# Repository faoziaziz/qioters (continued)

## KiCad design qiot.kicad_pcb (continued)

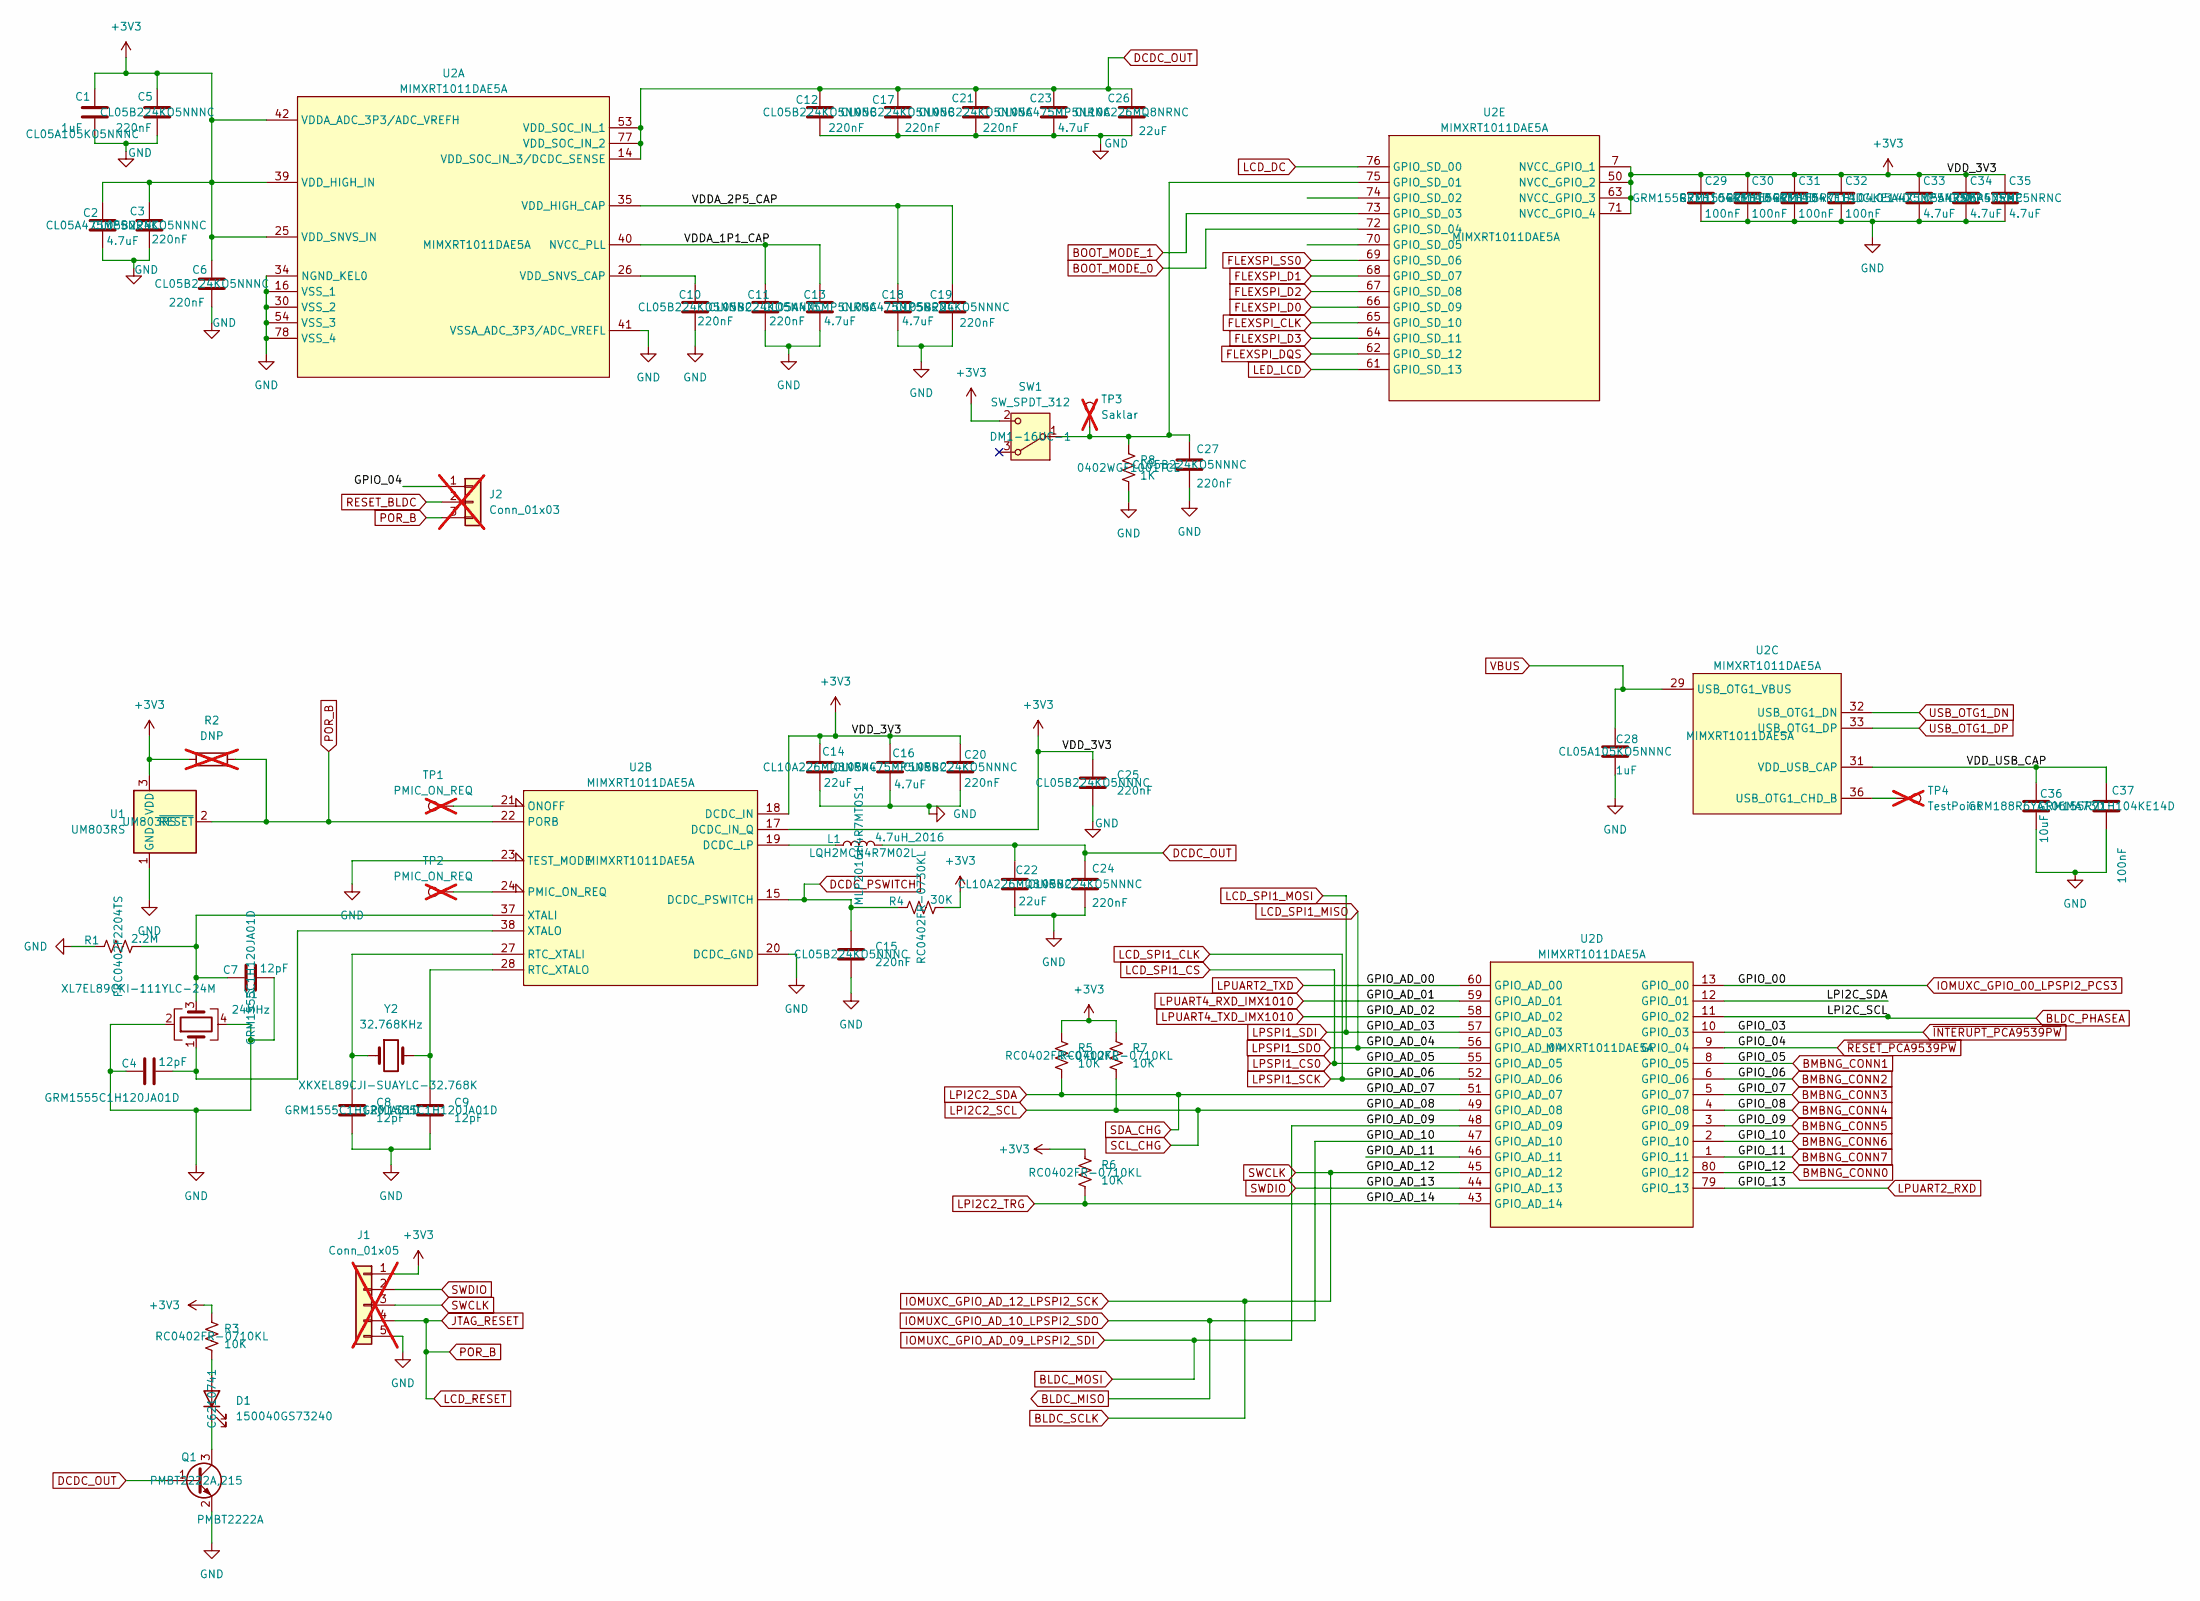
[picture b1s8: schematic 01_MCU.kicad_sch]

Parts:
C1, C28: 1uF; C_0402_1005Metric; Manufacturer_Part_Number CL05A105KO5NNNC; LCSC Part # C29266
C2, C13, C16, C18, C23, C33, C34, C35: 4.7uF; C_0402_1005Metric; Manufacturer_Part_Number CL05A475MP5NRNC; LCSC Part # C23733
C3, C5, C6, C10, C11, C12, C15, C17, C19, C20, C21, C24, C25, C27: 220nF; C_0402_1005Metric; Manufacturer_Part_Number CL05B224KO5NNNC; LCSC Part # C16772
C4, C7, C8, C9: 12pF; C_0402_1005Metric; Manufacturer_Part_Number GRM1555C1H120JA01D; LCSC Part # C76948
C14, C22, C26: 22uF; C_0603_1608Metric; Manufacturer_Part_Number CL10A226MQ8NRNC; LCSC Part # C59461
C29, C30, C31, C32, C37: 100nF; C_0402_1005Metric; Manufacturer_Part_Number GRM155R71H104KE14D; LCSC Part # C77020
C36: 10uF; C_0603_1608Metric; Manufacturer_Part_Number GRM188R6YA106MA73D; LCSC Part # C194427
D1: 150040GS73240; LED_0402_1005Metric; Manufacturer_Part_Number C6210741; LCSC Part # C6210741
J1: Conn_01x05; PinSocket_1x05_P2.54mm_Vertical; not fitted
J2: Conn_01x03; PinHeader_1x03_P2.54mm_Vertical; not fitted
L1: 4.7uH_2016; L_Murata_DFE201610P; Mfr. Part # LQH2MCN4R7M02L; LCSC Part # C383380
Q1: PMBT2222A; SOT-23; Manufacturer_Part_Number PMBT2222A,215; LCSC Part # C23869
R1: 2.2M; R_0402_1005Metric; Manufacturer_Part_Number FRC0402F2204TS; LCSC Part # C2998080
R2: DNP; R_0402_1005Metric; not fitted
R3, R5, R6, R7: 10K; R_0402_1005Metric; Manufacturer_Part_Number RC0402FR-0710KL; LCSC Part # C60490
R4: 30K; R_0402_1005Metric; Manufacturer_Part_Number RC0402FR-0730KL; LCSC Part # C138008
R8: 1K; R_0402_1005Metric; Manufacturer_Part_Number 0402WGF1001TCE; LCSC Part # C11702
SW1: SW_SPDT_312; SW_XKB_DM1-16UC-1; Manufacturer_Part_Number DM1-16UC-1; LCSC Part # C466019
TP1, TP2: PMIC_ON_REQ; TestPoint_Pad_D2.5mm; not fitted
TP3: Saklar; TestPoint_Pad_D2.5mm; not fitted
TP4: TestPoint; TestPoint_Pad_D2.5mm; not fitted
U1: UM803RS; SOT-23; Manufacturer_Part_Number UM803RS; LCSC Part # C620009
U2: MIMXRT1011DAE5A; MIMXRT1011DAE5A_NXP; Manufacturer_Part_Number MIMXRT1011DAE5A; LCSC Part # C1575810
Y1: 24MHz; OSC_XRCGB24M000F2P29R0; Mfr. Part # XRCGB24M000F2P29R0; LCSC Part # C2965580
Y2: 32.768KHz; CRYSTAL_FC-135 32.7680KA-AG3_EPS; Manufacturer_Part_Number XKXEL89CJI-SUAYLC-32.768K; LCSC Part # C7528807

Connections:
/01_MCU/GPIO_AD_11: U2.46 (GPIO_AD_11)
/01_MCU/LPI2C_SDA: U2.12 (GPIO_01)
/01_MCU/VDDA_1P1_CAP: C11.1, C13.1, U2.40 (NVCC_PLL)
/01_MCU/VDDA_2P5_CAP: C18.1, C19.1, U2.35 (VDD_HIGH_CAP)
/01_MCU/VDD_USB_CAP: C36.1, C37.1, U2.31 (VDD_USB_CAP)
BLDC_MISO: U2.47 (GPIO_AD_10)
BLDC_MOSI: U2.48 (GPIO_AD_09)
BLDC_PHASEA: U2.11 (GPIO_02)
BLDC_SCLK: J1.3, U2.45 (GPIO_AD_12)
BMBNG_CONN0: U2.80 (GPIO_12); also elsewhere on the board
BMBNG_CONN1: U2.8 (GPIO_05); also elsewhere on the board
BMBNG_CONN2: U2.6 (GPIO_06); also elsewhere on the board
BMBNG_CONN3: U2.5 (GPIO_07); also elsewhere on the board
BMBNG_CONN4: U2.4 (GPIO_08); also elsewhere on the board
BMBNG_CONN5: U2.3 (GPIO_09); also elsewhere on the board
BMBNG_CONN6: U2.2 (GPIO_10); also elsewhere on the board
BMBNG_CONN7: U2.1 (GPIO_11); also elsewhere on the board
BOOT_MODE_0: U2.72 (GPIO_SD_04); also elsewhere on the board
BOOT_MODE_1: U2.73 (GPIO_SD_03); also elsewhere on the board
DCDC_OUT: C12.1, C17.1, C21.1, C22.1, C23.1, C24.1, C26.1, L1.2, Q1.1 (B), U2.14 (VDD_SOC_IN_3/DCDC_SENSE), U2.53 (VDD_SOC_IN_1), U2.77 (VDD_SOC_IN_2)
DCDC_PSWITCH: C15.1, R4.1, U2.15 (DCDC_PSWITCH)
FLEXSPI_CLK: U2.65 (GPIO_SD_10); also elsewhere on the board
FLEXSPI_D0: U2.66 (GPIO_SD_09); also elsewhere on the board
FLEXSPI_D1: U2.68 (GPIO_SD_07); also elsewhere on the board
FLEXSPI_D2: U2.67 (GPIO_SD_08); also elsewhere on the board
FLEXSPI_D3: U2.64 (GPIO_SD_11); also elsewhere on the board
FLEXSPI_DQS: U2.62 (GPIO_SD_12)
FLEXSPI_SS0: U2.69 (GPIO_SD_06); also elsewhere on the board
IOMUXC_GPIO_00_LPSPI2_PCS3: U2.13 (GPIO_00)
JTAG_RESET: J1.4, J2.3, R2.2, U1.2 (~RESET), U2.22 (PORB); also elsewhere on the board
LCD_DC: U2.76 (GPIO_SD_00); also elsewhere on the board
LCD_SPI1_CLK: U2.52 (GPIO_AD_06); also elsewhere on the board
LCD_SPI1_CS: U2.55 (GPIO_AD_05); also elsewhere on the board
LCD_SPI1_MISO: U2.56 (GPIO_AD_04); also elsewhere on the board
LCD_SPI1_MOSI: U2.57 (GPIO_AD_03); also elsewhere on the board
LED_LCD: U2.61 (GPIO_SD_13); also elsewhere on the board
LPI2C2_SCL: R7.2, U2.49 (GPIO_AD_08); also elsewhere on the board
LPI2C2_SDA: R5.2, U2.51 (GPIO_AD_07); also elsewhere on the board
LPI2C2_TRG: R6.2, U2.43 (GPIO_AD_14)
LPUART2_RXD: U2.79 (GPIO_13)
LPUART2_TXD: U2.60 (GPIO_AD_00)
LPUART4_RXD_IMX1010: U2.59 (GPIO_AD_01); also elsewhere on the board
LPUART4_TXD_IMX1010: U2.58 (GPIO_AD_02); also elsewhere on the board
unnamed: D1.2 (A), R3.2
unnamed: D1.1 (K), Q1.3 (C)
unnamed: C27.1, R8.1, SW1.1 (B), TP3.1, U2.75 (GPIO_SD_01)
unnamed: C10.1, U2.26 (VDD_SNVS_CAP)
unnamed: L1.1, U2.19 (DCDC_LP)
unnamed: TP1.1, U2.21 (ONOFF)
unnamed: TP2.1, U2.24 (PMIC_ON_REQ)
unnamed: C8.1, U2.27 (RTC_XTALI), Y2.1
unnamed: C9.1, U2.28 (RTC_XTALO), Y2.2
unnamed: C7.1, R1.2, U2.37 (XTALI), Y1.3
unnamed: C4.2, U2.38 (XTALO), Y1.1
unnamed: TP4.1, U2.36 (USB_OTG1_CHD_B)
RESET_BLDC: J2.2
SWDIO: J1.2, U2.44 (GPIO_AD_13)
SYSN: C1.2, C2.2, C3.2, C4.1, C5.2, C6.2, C7.2, C8.2, C9.2, C10.2, C11.2, C12.2, C13.2, C14.2, C15.2, C16.2, C17.2, C18.2, C19.2, C20.2, C21.2, C22.2, C23.2, C24.2, C25.2, C26.2, C27.2, C28.2, C29.2, C30.2, C31.2, C32.2, C33.2, C34.2, C35.2, C36.2, C37.2, J1.5, Q1.2 (E), R1.1, R8.2, U1.1 (GND), U2.16 (VSS_1), U2.20 (DCDC_GND), U2.23 (TEST_MODE), U2.30 (VSS_2), U2.34 (NGND_KEL0), U2.41 (VSSA_ADC_3P3/ADC_VREFL), U2.54 (VSS_3), U2.78 (VSS_4), Y1.2, Y1.4; also elsewhere on the board
USB_OTG1_DN: U2.32 (USB_OTG1_DN); also elsewhere on the board
USB_OTG1_DP: U2.33 (USB_OTG1_DP); also elsewhere on the board
VBUS: C28.1, U2.29 (USB_OTG1_VBUS)
~INTERUPT_PCA9539PW: U2.10 (GPIO_03); also elsewhere on the board
~RESET_PCA9539PW: J2.1, U2.9 (GPIO_04); also elsewhere on the board

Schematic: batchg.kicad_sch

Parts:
C52, C56, C58, C59: 10uF; C_0603_1608Metric; Manufacturer_Part_Number GRM188R6YA106MA73D; LCSC Part # C194427
C53: 150uF; CP_Elec_10x10.5; Manufacturer_Part_Number EEEFK1H151P; LCSC Part # C413508
C54: 1uF; C_0402_1005Metric; Manufacturer_Part_Number CL05A105KO5NNNC; LCSC Part # C29266
C55: 100nF; C_0402_1005Metric; Manufacturer_Part_Number GRM155R71H104KE14D; LCSC Part # C77020
C57: 22nF; C_0402_1005Metric; Manufacturer_Part_Number GRM155R71H223KA12D; LCSC Part # C77023
C60: 150uF; CP_Elec_10x10.5; Manufacturer_Part_Number EEEFK1H151P; JLCPARTS EEEFK1H151P
D7: 150040GS73240; LED_0402_1005Metric; Manufacturer_Part_Number C6210741; LCSC Part # C6210741
D8, D9, D10: CUS05S40; D_SOD-323; Manufacturer_Part_Number CUS05S40.H3F; LCSC Part # C2762696
J4: PJ-102AH; DC-IN-TH_PJ-102AH; Manufacturer_Part_Number PJ-102AH; LCSC Part # C3096093
J13, J14: CELLS1; PinHeader_2x03_P2.54mm_Vertical; not fitted
J15, J16: Conn_01x03; PinHeader_1x03_P2.54mm_Vertical; not fitted
L2: 6.8uH; L_Murata_DFE201610P; PartNum MAI201610S-6R8MT; LCSC Part # C41405888
Q9, Q10: IRLZ44NSTRL(UMW); TO-263-2; Manufacturer_Part_Number IRLZ44NSTRL(UMW); LCSC Part # C42370422
R44, R48, R49: 100K; R_0402_1005Metric; Manufacturer_Part_Number RC0402FR-07100KL; LCSC Part # C60491
R45: 2.2K; R_0402_1005Metric; Manufacturer_Part_Number RC0402FR-072K2L; LCSC Part # C114762
R46, R50, R53: 10K; R_0402_1005Metric; Manufacturer_Part_Number RC0402FR-0710KL; LCSC Part # C60490
R47, R52: 4.7K; R_0402_1005Metric; Manufacturer_Part_Number RC0402FR-074K7L; LCSC Part # C105871
R51: 2.49; R_0402_1005Metric; Manufacturer_Part_Number CRCW04022R49FKED; LCSC Part # C2085509
R54: 63.4K; R_0402_1005Metric; Manufacturer_Part_Number FRC0402F6342TS; LCSC Part # C2933107
R55: OPT; R_0402_1005Metric; not fitted
R56: 0; R_0402_1005Metric; Manufacturer_Part_Number RC0402FR-070RL; LCSC Part # C106231
R57, R59: 0.01; R_0402_1005Metric; Manufacturer_Part_Number RC0402FR-0710ML; LCSC Part # C138067
R58: 10; R_0402_1005Metric; Manufacturer_Part_Number FRC0402F10R0TS; LCSC Part # C2906862
U6: LTC4162EUFD; 05-08-1712_ADI; Manufacturer_Part_Number LTC4162EUFD; LCSC Part # C3681528

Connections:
BATSENS_CHG: C59.1, C60.1, R58.2, R59.2, U6.19 (BATSENS+); also elsewhere on the board
DVCC: R44.1, R45.1, R47.2, R52.1, U6.15 (DVCC)
INTVcc: C52.1, D10.2 (A), J13.1, J14.2, U6.2 (INTVCC)
LPI2C2_SCL: R47.1, U6.13 (SCL); also elsewhere on the board
LPI2C2_SDA: R52.2, U6.14 (SDA); also elsewhere on the board
NTC: R56.2
NTCBIAS: R53.1, U6.9 (NTCBIAS)
NTCwiper: J15.1
unnamed: C53.1, R51.2
unnamed: C57.2, L2.1, U6.25 (SW), U6.26 (SW)
unnamed: D7.2 (A), R45.2
unnamed: D8.2 (A), Q9.2 (D), R57.2, U6.5 (CLP)
unnamed: D9.2 (A), R58.1, U6.20 (CSN)
unnamed: D9.1 (K), L2.2, Q10.3 (S), R59.1, U6.21 (CSP)
unnamed: C57.1, D10.1 (K), U6.1 (BOOST)
unnamed: J13.2, J13.4, J13.6, R49.1
unnamed: C54.1, J13.3, J14.4, U6.8 (VCC2P5)
unnamed: J14.1, J14.3, J14.5, R48.1
unnamed: J15.2, U6.10 (NTC)
unnamed: J15.3, J16.2, R53.2
unnamed: J16.1, R46.1
unnamed: J16.3, R55.2, R56.1
unnamed: Q9.1 (G), U6.6 (INFET)
unnamed: Q10.1 (G), U6.22 (BATFET)
unnamed: R49.2, U6.17 (CELLS0)
unnamed: R48.2, U6.18 (CELLS1)
unnamed: R54.1, U6.11 (RT)
SYNC: R50.1, U6.16 (SYNC)
SYSN: C52.2, C53.2, C54.2, C55.2, C56.2, C58.2, C59.2, C60.2, J4.3, J13.5, J14.6, R46.2, R50.2, R54.2, R55.1, U6.23 (PGND), U6.24 (PGND), U6.29 (AGND); also elsewhere on the board
VIN_CHG: C55.1, J4.1, Q9.3 (S), R51.1, U6.7 (VIN)
VOUT_BATCHG: C56.1, C58.1, D8.1 (K), Q10.2 (D), R57.1, U6.3 (VOUTA), U6.4 (CLN), U6.27 (VOUT), U6.28 (VOUT); also elsewhere on the board
~SMBALERT: D7.1 (K), R44.2, U6.12 (~SMBALERT)

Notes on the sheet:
goint to bAttmon
4.5V <-> 36 V

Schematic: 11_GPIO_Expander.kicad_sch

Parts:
J30: BAMBANG_CONNECTOR; PinHeader_1x16_P2.54mm_Vertical; not fitted
R92, R93: 10K; R_0402_1005Metric; Manufacturer_Part_Number RC0402FR-0710KL; LCSC Part # C60490
U14: PCA9539PW_118; SOP65P640X110-24N; MPN PCA9539PW,118; LCSC Part # C2687996

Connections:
BMBNG_CONN0: J30.9; also elsewhere on the board
BMBNG_CONN1: J30.10; also elsewhere on the board
BMBNG_CONN2: J30.11; also elsewhere on the board
BMBNG_CONN3: J30.12; also elsewhere on the board
BMBNG_CONN4: J30.13; also elsewhere on the board
BMBNG_CONN5: J30.14; also elsewhere on the board
BMBNG_CONN6: J30.15; also elsewhere on the board
BMBNG_CONN7: J30.16; also elsewhere on the board
LPI2C2_SCL: U14.23 (SDA); also elsewhere on the board
LPI2C2_SDA: U14.22 (SCL); also elsewhere on the board
MOTOR_DIR: U14.18 (IO1_5); also elsewhere on the board
MOTOR_EN: U14.13 (IO1_0); also elsewhere on the board
MOTOR_M0: U14.16 (IO1_3); also elsewhere on the board
MOTOR_M1: U14.15 (IO1_2); also elsewhere on the board
MOTOR_M2: U14.14 (IO1_1); also elsewhere on the board
MOTOR_RST: U14.19 (IO1_6); also elsewhere on the board
MOTOR_SLP: U14.20 (IO1_7); also elsewhere on the board
MOTOR_STP: U14.17 (IO1_4); also elsewhere on the board
unnamed: J30.1, U14.4 (IO0_0)
unnamed: J30.2, U14.5 (IO0_1)
unnamed: J30.3, U14.6 (IO0_2)
unnamed: J30.4, U14.7 (IO0_3)
unnamed: J30.5, U14.8 (IO0_4)
unnamed: J30.6, U14.9 (IO0_5)
unnamed: J30.7, U14.10 (IO0_6)
unnamed: J30.8, U14.11 (IO0_7)
SYSN: U14.2 (A1), U14.12 (VSS), U14.21 (A0); also elsewhere on the board
~INTERUPT_PCA9539PW: R93.2, U14.1 (~INT); also elsewhere on the board
~RESET_PCA9539PW: R92.2, U14.3 (~RESET); also elsewhere on the board

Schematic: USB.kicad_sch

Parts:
C38: 22uF; C_0603_1608Metric; Manufacturer_Part_Number CL10A226MQ8NRNC; LCSC Part # C59461
D2, D3: PMEG3020EH; D_SOD-123F; Manufacturer_Part_Number PMEG3020EH; LCSC Part # C167645
D4: 150040GS73240; LED_0402_1005Metric; Manufacturer_Part_Number C6210741; LCSC Part # C6210741
J3: TYPE-C-31-M-12; HRO_TYPE-C-31-M-12; PARTREV 2020.12.08; LCSC Part # C165948
Q2: PMBT2222A; SOT-23; Manufacturer_Part_Number PMBT2222A,215; LCSC Part # C23869
R9, R10: 5.1K; R_0402_1005Metric; Manufacturer_Part_Number RC0402FR-075K1L; LCSC Part # C105872
R11: 2.7K; R_0402_1005Metric; Manufacturer_Part_Number RC0402FR-072K7L; LCSC Part # C138017
R12: 1K; R_0402_1005Metric; Manufacturer_Part_Number 0402WGF1001TCE; LCSC Part # C11702

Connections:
/02_USB/VBUS_USB: D2.2 (A), D3.2 (A), J3.A4_B9 (VBUS), J3.B4_A9 (VBUS), R11.2
unnamed: D4.1 (K), R12.2
unnamed: J3.A5 (CC1), R9.2
unnamed: J3.B5 (CC2), R10.2
unnamed: Q2.1 (B), R11.1
unnamed: Q2.3 (C), R12.1
SYSN: C38.2, J3.A1_B12 (GND), J3.B1_A12 (GND), J3.S1 (SHIELD), J3.S2 (SHIELD), J3.S3 (SHIELD), J3.S4 (SHIELD), Q2.2 (E), R9.1, R10.1; also elsewhere on the board
USB_OTG1_DN: J3.A7 (DN1), J3.B7 (DN2); also elsewhere on the board
USB_OTG1_DP: J3.A6 (DP1), J3.B6 (DP2); also elsewhere on the board
VSYS_USB: C38.1, D2.1 (K), D3.1 (K); also elsewhere on the board

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
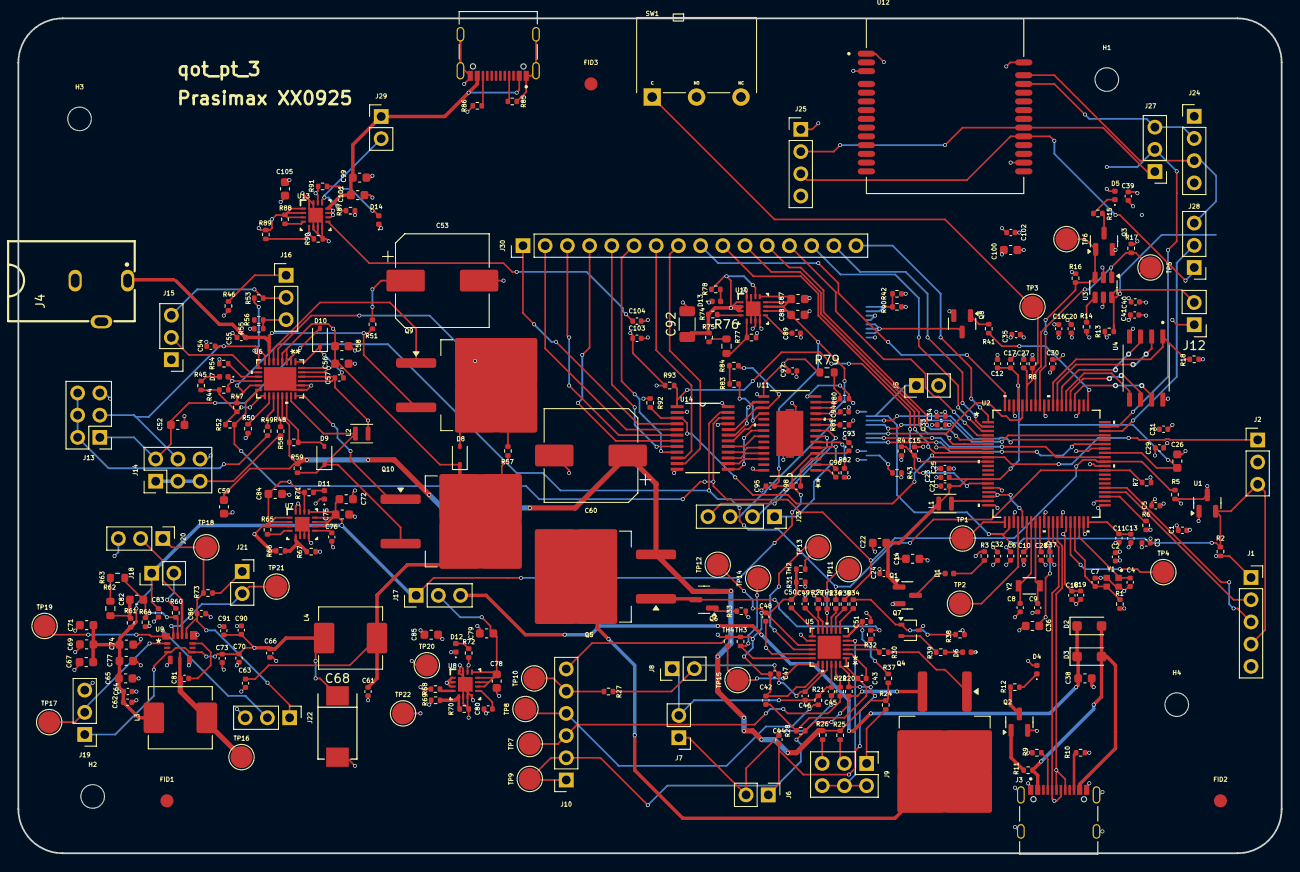
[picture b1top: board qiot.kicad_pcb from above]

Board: 4 copper layers, 144.5 x 95.5 mm, 304 parts (1 on the bottom side), 205 nets.

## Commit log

2025-04-20 siapa presiden
2025-04-20 add base
2025-04-20 mera
2025-04-28 add revision to motor
2025-05-01 del some
2025-05-18 dad
    da
2025-10-26 gema
2026-03-31 some
2026-03-31 add submodule
